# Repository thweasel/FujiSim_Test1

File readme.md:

# FujiNet Z80 simulation

The repo contains a SimulIDE simulator circuit with an Ardunio Mega to simulate Z80 and ESP signalling to the proposed bus interface.

Platform IO should be used within Visual Code to compile the project which is based on Arduino libraries.

## SimulIDE simulation settings

**SimulIDE Version0.4.15SR10**

To accurately simulate the SPI timing the properties of the simulation need to be edited before running. The "Simu Step ns" needs to be set to 10 in SimulIDE (right click empty diagram space, select properties from pop up menu). If simulation step time is not set correctly, then the ESP simulation will see bits missing when reading the Shift registers as the Clock and data signalling slips.

Don't forget to load the Firmware file into the Arduino! PlatformIO compiles the Arduino code to ./.pio/megaatmega2560/firmware.hex, when you click Build (not Build and program unless you are using real hardware!)

## KiCad ##

**KiCad version 7**

Going forward there are going to be different ways that the modules can be implemented and built. Therefore, a set of KiCad projects are in a modules folder, and then there is a folder for libraries for symbols/footprints; these are the building blocks. 

Each module project should have 2 schematics. The main project schematic has Pin headers etc. for a (test) PCB and a hierarchical schematic (not a project just a file) that contains the module's circuit. The module's hierarchical schematic file should not contain any connectors or "PCB stuff" just the parts needed for its function. So when making an adaptor the nested hierarchical schematic can be imported this hierarchical schematic without the extra "PCB stuff" cluttering the adaptor project PCBs. Module projects do not need a PCB design as they are imported into other projects that implement the PCB design and associated connectors etc. However, I like the idea of the modules being projects which have a PCB design to create a physical implementation for testing. In time all the modules could follow some common standard for PCB implementation these could be built and wired up ad-hoc.

A reference design is in the root KiCad folder, this shows how everything should connect up to make an adapter. There shouldn't really be a PCB for the reference design as the PCB design can (and did) influence the schematic. The reference design should be a pure, readable and simple expression of the requirements. So going forward a KiCad project should be created for the adaptor being built (in the adaptors folder), a simple way to copy all the settings is to save as from a similar project (e.g. template project). Now the modules schematics can be added to the adaptor project hierarchical schematics, add their hierarchical pins and wire/label as required.

If an adaptor uses a daughter board, then sub-projects in the adapter project need to be created (so they have their own PCB design). The sub-project is imported to the adaptor's main project as a hierarchical schematic so that the Electronic Rule Checker (ERC) can be used to validate the design.  Don't try to mark one-eye ball an adaptor design there are multiple busses and logic signals, and it's not far off a small computer; ERC is a valuable tool so use it. Another trick is to make use of the BUS net Class directives which apply styling to the connected bus, if a connection is missing there is no styling applied. I like to make it easy to see when things aren't connected as sometimes the ERC won't report a problem (more than one pin is connected makes it valid, even if it should be 3 pins connected).

## PCB fabrication with a 3018 CNC mill

The software pipeline:
- KiCad PCB design (export Gerber and Drill files)
- pcb2gcode (CAM, gerber to gcode)
- Universal Gcode Sender (runs the CNC mill controller)

The size and accuracy of the mill determine the PCB design rules to be used in the KiCad board setup. 

After trial and error, the following minimum limits have been found. A 0.5mm end mill (cutter) requires at a minimum, 0.4mm tracks and 0.6mm clearances. (This may change with pcb2gcode and some "git-gud"). With a 200-watt spindle motor, the following speeds and feeds for drilling and milling with a 0.5mm end mill.

Drilling
- Z cut -2mm
- Z Feedrate 30
- Spindle Speed 600 (~60% power)

Milling
- Z cut -0.15mm (board thickness varies)
- X-Y Feedrate 60 (20 or 40)
- Z Feedrate 30
- Spindle speed 800 (~80% power)

Going slower seems to be better for accuracy and success. Running the milling at max spindle speed and -1.5 cut resulted in a snapped 0.5mm end mill. Also, there is a lot of noise/vibration which makes the cutting just sound wrong.

The choice of tool for cutting the isolation paths seems to be split between V-bits and tiny straight-end mills. V-bits have a tip as narrow as 0.1mm but widen based on the angle (degrees) of the V. Assuming a perfectly flat board of even thickness, the tip + width at depth (0.1mm) isolation paths can be cut; assume a width of ~0.2mm approximately. However, perfect doesn't exist, the bit moves as Z height but the surface height changes (PCB thickness, bowing etc.). Therefore, the cut width changes as the V shape angle produces wider cuts as the tip moves deeper into the material. An end mill has a straight edge so cuts consistently at all depths below the surface. The only concern is cutting too deep and breaking the end mill, which is why a 0.5mm bit is used. End mills or Ball cutters go down to 0.2mm, but breakage risks increase. There is a similar problem with V bits, a 20-degree angle has a weaker tip than a 60-degree angle V bit. A wider angle V bit cut widens quicker with slight changes in depth. There is no perfect tool, just compromises and different workflows.

To counter problems with Vbits and depth of cut, Universal Gcode Sender has a plugin called "AutoLeveler". This plugin probes the height of the PCB at some given intervals. A height map is generated and the Z positions in the Gcode are modified. Thus, adding to the process of milling per side, probing pass and transformation of gcode. The accuracy of the trace is subject to the resolution of the probing, high accuracy means probing more points (long time). To conclude, there is room to achieve thinner track and clearance but for now, a simpler reliable approach trumps mastery of PCB milling.

Milling two-sided PCBs require the board to be flipped. This is an immediate alignment challenge which needs some thought. There are limitations imposed by CAM software features and the size of the CNC mill. Typically, the method seems to be prescribed by the CAM software. FlatCAM does inbox flips, the board is in the same place on the bed. To do this FlatCAM provides support to flip/mirror one of the Gerbers, alignment drill holes can be easily added. However, FlatCAM is too manual and buggy. 

Pcb2gcode enables "millproject" config files to be set up and reused between projects. The flip method used is a page turn by default, which requires the bed to be twice the size of the PCB. With a small bed and a big board, an in-place flip can be achieved by re-zeroing the origin on the X-axis after the flip.  Ideally, a jig should be used to maintain X-Y alignment or alternatively a pair of alignment holes evenly spaced from the centre lines. To make the flip alignment accurate an alignment hole can be drilled at 0,0 on the front; when flipped re-align to the hole and reset X 0. If you don't want to make holes in a PCB that is cut accurately to size, then zero on the corners (with the same tool fitted each time).

### KiCad PCB design/settings

Before laying out the PCB you need to set up the board settings, Design Rules and Net Classes. these should be set based on the achievable tollerances of the milling process.

Auto routing (FreeRouting) ignores the Design Rules, it only seems to follow NetClass rules, Edges and Margins (Rule areas on the margin layer). Therefore, you should fully define the board before placing components!

The process sets are:
Configure Design Rules and Net Classes
Draw an Edge box to the size of the PCB
Set Origin (file/drill/sheet) in the top left of the Edge box - place a *VIA on this spot
Create Margin boxes (+2mm) on the edges (Rule Area)
Layout components
Route tracks
Export Gerber and drill files (include the origins)
Export SVG as a CNC reference. F.Cu, B.Cu, User.Drawings, Edge.Cuts, F.Fab, B.Fab

*Directly placing a VIA on the Origin is blocked if it is in the margin. To get round this place the VIA outside the margin and move it to the Origin, this is permitted. Else you could adjust the shape of the marging and expose the corner.

Your PCB should have an Edge box the size of the PCB (stock or cut out). Marked out margins for Freerouting, 2mm seems reasonable. The Origin for sheets and files needs to be set at the top left of the Edge box. Origin can be corrected in pcb2gcode and milling just saves effort to do it right. Export to Gerber (Fabrication output), make sure "Use drill/place file origin" is checked. Hit Plot and Generate Drill Files. If you want to be tidy, export only the F.Cu, B.CU, and Edge_Cuts. You have a PCB file set to run through pcb2gcode.

The KiCad process is done!

### pcb2gcode CAM 

A "millproject" needs to be configured which enables milling a PCB with the Design Rules defined in KiCad. Yep, this is a circular dependency! 

Each Gerber needs to be addressed directly in the millproject file. Given the KiCad naming scheme, a bash script with a command line config can be used to wildcard the files. E.g. "pcb2gcode --front=*-F_Cu.gbr".

Read the wiki to create the millproject file https://github.com/pcb2gcode/pcb2gcode/wiki/Manual

Examples can be found in the pcb2gcode folder.

### Milling procedure

Set up a jig on the bed to hold the PCB.

Start with the front processes, which all have positive X co-ordinates

**Alignment**
- Align the mill and zero on the origin TOP-LEFT (same as KiCad)
- Use the PCB corner (marker pen) OR drill an alignment hole for the origin

**Drilling - front**
- Use drill bits that are the same length butted up in the collet, save  zeroing the Z axis per bit.
- Fit the first Tool (drill bit) in drill.ngc
- Touch the bit on the surface of the board and set Z to zero
- Run the drill.ngc
- Change bits as prompted.

**Milling - front**
- Fit the 0.5mm end mill
- Touch bit on the PCB surface and 0 Z axis
- Run Front.ngc

**Flip on Y (left to right)**
- The default flip/mirror axis in pcb2gcode is along the left edge of the - PCB, "turning a page in a book".
- Measure the X-axis length, move the mill from 0,0 lenght+X
- The mill should now be aligned to the TOP-RIGHT corner, opposite the origin used for the front.
- Tune positioning
- RESET X to 0

All cuts on the Back.ngc have a negative X coordinate so the mill runs from right to left.

**Milling - back**
- Fit the 0.5mm end mill
- Touch bit on the PCB surface and 0 Z axis
- Run Back.ngc

**Cut out - optional**
- Fit a cutting end mill (3.127mm)
- Touch bit on the PCB surface and 0 Z axis
- Run Outline.ngc

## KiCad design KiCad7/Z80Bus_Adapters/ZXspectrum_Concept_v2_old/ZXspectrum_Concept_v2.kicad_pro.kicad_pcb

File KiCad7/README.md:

# KiCad projects

Folders:

**Adapters** projects to make FujiNet adapters for different machines.

**Modules** parts to import into adapters for common functions e.g. SPI bus.

**Modules/*_impl** modules implemented as stand-alone PCBs with connectors

**ReferenceDesign** is an example of a completed adapter (schematic) for a ZX spectrum. This is the current concept design.

## New projects and path management

Some KiCad referencing information because managing paths is a tad annoying. Use relative pathing if you want anyone to open something you made. To do this all paths should start ${KIPRJMOD} which is the environment variable for the project folder ../ will take you back one layer as expected.

If you want to start a new Module or Adapter then you should open the template project and SAVE AS "name". This will copy the template and setting for you, and then there is less to set up.  Setting up from scratch requires libraries importing, Net classes, buses, PCB settings etc set up.

### Symbols

Name: esp32-wrover
Path: ${KIPRJMOD}/../../FujiNet_KiCadLibs/esp32-wrover-kicad-master/esp32-wrover.lib

Name: FujiNet_Memory_RAM
Path: ${KIPRJMOD}/../../FujiNet_KiCadLibs/FujiNet_Memory_RAM.kicad_sym

### Footprints
Name: esp32-wrover
Path: ${KIPRJMOD}/../../FujiNet_KiCadLibs/esp32-wrover-kicad-master/esp32-wrover.pretty

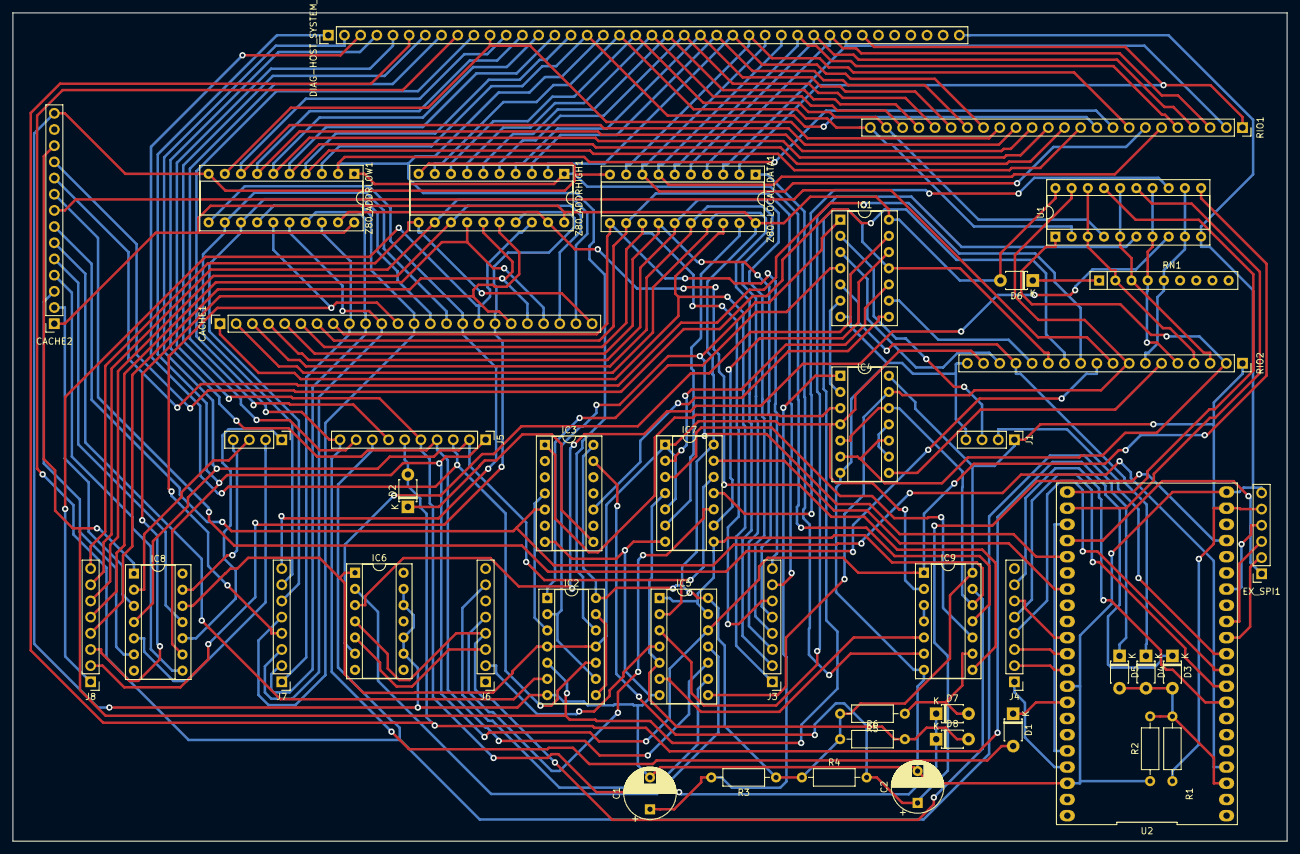
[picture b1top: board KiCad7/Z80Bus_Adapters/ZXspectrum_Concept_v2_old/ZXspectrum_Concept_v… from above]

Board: 2 copper layers, 200.0 x 130.0 mm, 45 parts (0 on the bottom side), 139 nets.

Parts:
C1, C2: 10UF; CP_Radial_D8.0mm_P5.00mm
CACHE1: Conn_01x24_Socket; PinSocket_1x24_P2.54mm_Vertical
CACHE2: Conn_01x14_Socket; PinSocket_1x14_P2.54mm_Vertical
D1, D2, D3, D4, D5, D6, D7, D8: 1N4148; D_T-1_P5.08mm_Horizontal
DIAG-HOST_SYSTEM_BUS1: DIAG-HOST_SYSTEM_BUS; PinHeader_1x40_P2.54mm_Vertical
EX_SPI1: PinSocket_2.54mm; PinSocket_1x06_P2.54mm_Vertical
IC1: 7404N; DIP-14_W7.62mm_Socket
IC2, IC5, IC7, IC9: 74HC32N; DIP-14_W7.62mm_Socket
IC3: 7474N; DIP-14_W7.62mm_Socket
IC4, IC6, IC8: 74HC08N; DIP-14_W7.62mm_Socket
J1: PinHeader_2.54mm; PinHeader_1x04_P2.54mm_Vertical
J3: LOCAL_D; PinHeader_1x08_P2.54mm_Vertical
J4: ESP_SPI_INT; PinHeader_1x08_P2.54mm_Vertical
J5: Z80_CONTROL; PinHeader_1x10_P2.54mm_Vertical
J6: ESP_CONTROL; PinHeader_1x08_P2.54mm_Vertical
J7: LOCAL_A-L; PinHeader_1x08_P2.54mm_Vertical
J8: LOCAL_A-H; PinHeader_1x08_P2.54mm_Vertical
LOCAL_CONTROL1: LOCAL_CONTROL; PinHeader_1x04_P2.54mm_Vertical
R1, R2, R3, R4: 22K; R_Axial_DIN0207_L6.3mm_D2.5mm_P10.16mm_Horizontal
R5, R6: 10K; R_Axial_DIN0207_L6.3mm_D2.5mm_P10.16mm_Horizontal
RIO1: Conn_01x24_Socket; PinSocket_1x24_P2.54mm_Vertical
RIO2: Conn_01x18_Socket; PinSocket_1x18_P2.54mm_Vertical
RN1: 4609M-101-103LF; R_Array_SIP9
U1: 74HC244N; DIP-20_W7.62mm_Socket
U2: FREENOVE_ESP32-WROVER-DEV
Z80-LOCAL_DATA1, Z80_ADDRHIGH1, Z80_ADDRLOW1: 74HC245N; DIP-20_W7.62mm_Socket

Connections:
+5V: CACHE2.1, D6.2 (A), EX_SPI1.5, IC1.14 (VCC), IC2.14 (VCC), IC3.14 (VCC), IC4.14 (VCC), IC5.14 (VCC), IC7.14 (VCC), IC9.14 (VCC), J1.1, R1.2, R3.1, R4.1, R5.2, R6.1, RIO2.1, U1.20 (VCC), U2.20 (+5V), Z80-LOCAL_DATA1.20 (VCC), Z80_ADDRHIGH1.20 (VCC), Z80_ADDRLOW1.20 (VCC)
/CACHE connector/CACHE_CONTROL.A16: CACHE2.2, IC8.3
/CACHE connector/CACHE_CONTROL.CS: CACHE2.5, IC8.11
/CACHE connector/CACHE_CONTROL.DATASTATUS+PERM_Z80_IORQ: CACHE2.6, IC2.6
/CACHE connector/CACHE_CONTROL.OE: CACHE2.4, IC8.8
/CACHE connector/CACHE_CONTROL.WE: CACHE2.3, IC8.6
/CACHE connector/CACHE_DATASTATUS: CACHE2.12, IC1.11, IC2.5, IC8.1, RIO2.13
/CACHE connector/CACHE_SEL_0: CACHE2.8, RIO2.9
/CACHE connector/CACHE_SEL_1: CACHE2.9, RIO2.10
/CACHE connector/CACHE_SEL_2: CACHE2.10, RIO2.11
/CACHE connector/CACHE_SEL_3: CACHE2.11, RIO2.12
/CACHE connector/LOCAL_A0: CACHE1.9, J7.1, Z80_ADDRLOW1.18 (B0)
/CACHE connector/LOCAL_A1: CACHE1.10, J7.2, Z80_ADDRLOW1.17 (B1)
/CACHE connector/LOCAL_A2: CACHE1.11, J7.3, Z80_ADDRLOW1.16 (B2)
/CACHE connector/LOCAL_A3: CACHE1.12, J7.4, Z80_ADDRLOW1.15 (B3)
/CACHE connector/LOCAL_A4: CACHE1.13, J7.5, Z80_ADDRLOW1.14 (B4)
/CACHE connector/LOCAL_A5: CACHE1.14, J7.6, Z80_ADDRLOW1.13 (B5)
/CACHE connector/LOCAL_A6: CACHE1.15, J7.7, Z80_ADDRLOW1.12 (B6)
/CACHE connector/LOCAL_A7: CACHE1.16, J7.8, Z80_ADDRLOW1.11 (B7)
/CACHE connector/LOCAL_A8: CACHE1.17, J8.1, Z80_ADDRHIGH1.18 (B0)
/CACHE connector/LOCAL_A9: CACHE1.18, J8.2, Z80_ADDRHIGH1.17 (B1)
/CACHE connector/LOCAL_A10: CACHE1.19, J8.3, Z80_ADDRHIGH1.16 (B2)
/CACHE connector/LOCAL_A11: CACHE1.20, J8.4, Z80_ADDRHIGH1.15 (B3)
/CACHE connector/LOCAL_A12: CACHE1.21, J8.5, Z80_ADDRHIGH1.14 (B4)
/CACHE connector/LOCAL_A13: CACHE1.22, J8.6, Z80_ADDRHIGH1.13 (B5)
/CACHE connector/LOCAL_A14: CACHE1.23, J8.7, Z80_ADDRHIGH1.12 (B6)
/CACHE connector/LOCAL_A15: CACHE1.24, J8.8, Z80_ADDRHIGH1.11 (B7)
/CACHE connector/LOCAL_D0: CACHE1.1, J3.1, Z80-LOCAL_DATA1.18 (B0)
/CACHE connector/LOCAL_D1: CACHE1.2, J3.2, Z80-LOCAL_DATA1.17 (B1)
/CACHE connector/LOCAL_D2: CACHE1.3, J3.3, Z80-LOCAL_DATA1.16 (B2)
/CACHE connector/LOCAL_D3: CACHE1.4, J3.4, Z80-LOCAL_DATA1.15 (B3)
/CACHE connector/LOCAL_D4: CACHE1.5, J3.5, Z80-LOCAL_DATA1.14 (B4)
/CACHE connector/LOCAL_D5: CACHE1.6, J3.6, Z80-LOCAL_DATA1.13 (B5)
/CACHE connector/LOCAL_D6: CACHE1.7, J3.7, Z80-LOCAL_DATA1.12 (B6)
/CACHE connector/LOCAL_D7: CACHE1.8, J3.8, Z80-LOCAL_DATA1.11 (B7)
/CACHE connector/Z80_HARDLOCK: CACHE2.7, IC3.5 (Q), U2.4 (GPIO39)
/CORE/ESP_HARDLOCK: IC1.1, IC2.2, IC2.9, U2.26 (GPIO2)
/CORE/ESP_INT: D3.2 (A), D4.2 (A), D5.2 (A), R1.1, R2.2, U2.3 (GPIO36)
/CORE/ESP_PULSE: J1.2, U2.11 (GPIO27)
/CORE/ESP_ROMSEL_0: U1.15 (2A1), U2.23 (GPIO7)
/CORE/ESP_ROMSEL_1: U1.17 (2A0), U2.22 (GPIO6)
/CORE/ESP_ROM_WR_PROTECT: IC7.13, U2.28 (GPIO4)
/CORE/ESP_SPI_INT.CE: J4.6, U2.31 (GPIO5)
/CORE/ESP_SPI_INT.MISO: J4.2, U2.33 (GPIO19)
/CORE/ESP_SPI_INT.MOSI: J4.1, U2.39 (GPIO23)
/CORE/ESP_SPI_INT.OE: J4.7, U2.8 (GPIO33)
/CORE/ESP_SPI_INT.PL: J4.5, U2.9 (GPIO25)
/CORE/ESP_SPI_INT.SCK: J4.3, U2.32 (GPIO18)
/CORE/ESP_SPI_INT.STC: J4.4, U2.10 (GPIO26)
/CORE/ESP_WAIT_RESET: C2.1, IC3.13 (~R), R4.2, U2.18 (GPIO11)
/CORE/EX_MISO: EX_SPI1.3, U2.13 (GPIO12)
/CORE/EX_MOSI: EX_SPI1.4, U2.15 (GPIO13)
/CORE/EX_SCK: EX_SPI1.2, U2.12 (GPIO14)
/CORE/EX_SS: EX_SPI1.1, U2.25 (GPIO8)
/CORE/SD_CARD_SS: U2.24 (GPIO15), U2.38 (GPIO22)
/CORE/Z80_HARDLOCK_RESET: D4.1 (K), IC1.5, RIO2.15
/GLUE/!ESP_HARDLOCK: IC1.2, J1.3
/GLUE/CLR_Z80_HARDLOCK: IC3.1 (~R), IC4.3
/GLUE/ESP_IOD_CONFIG: IC4.5, IC4.12, IC5.1, IC5.13, IC7.8, IC9.12
/GLUE/PERM_Z80_IORQ: IC2.4, IC2.11, IC4.4, IC6.1, IC7.1, IC7.5, IC8.12, IC9.2, RIO2.17
/GLUE/PRE_Z80_HARDLOCK: IC2.3, IC3.4 (~S)
/GLUE/RIO CONTROL/ROM_WR_PROTECT+Z80_WR: IC7.11, U1.13 (2A2)
/GLUE/RIO CONTROL/Z80_RD+ESP_IOD_CONFIG+PERM_Z80_IORQ: IC6.3, U1.8 (1A3)
/GLUE/RIO CONTROL/Z80_WR+ESP_IOD_CONFIG: IC5.3, U1.6 (1A2)
/GLUE/RIO_CONTROL.A14: RIO2.4, RN1.2 (R1), U1.3 (2Y0), U1.18 (1Y0)
/GLUE/RIO_CONTROL.A15: RIO2.3, RN1.3 (R2), U1.5 (2Y1), U1.16 (1Y1)
/GLUE/RIO_CONTROL.A16: IC4.6, IC4.10, RIO2.2, U1.1 (1OE)
/GLUE/RIO_CONTROL.CE: IC4.8, RIO2.6
/GLUE/RIO_CONTROL.OE: RIO2.7, RN1.5 (R4), U1.9 (2Y3), U1.12 (1Y3)
/GLUE/RIO_CONTROL.ROM_RDY: IC4.13, IC5.8, RIO2.8, U1.19 (2OE)
/GLUE/RIO_CONTROL.WE: RIO2.5, RN1.4 (R3), U1.7 (2Y2), U1.14 (1Y2)
/GLUE/WAIT_IO: IC1.9, RIO2.14
/GLUE/Z80 BUS CONTROL/!CACHE_DATASTATUS: IC1.10, IC7.2
/GLUE/Z80 BUS CONTROL/Z80_ADD_CONNECT: D7.2 (A), IC9.9, R5.1
/GLUE/Z80 BUS CONTROL/Z80_DATA_CONNECT: D8.2 (A), IC5.5, IC7.4, R6.2
/GLUE/Z80_BUS_CONTROL.Z80_ADD_DIR: IC9.11, Z80_ADDRHIGH1.1 (A->B), Z80_ADDRLOW1.1 (A->B)
/GLUE/Z80_BUS_CONTROL.Z80_ADD_OE: IC9.8, Z80_ADDRHIGH1.19 (CE), Z80_ADDRLOW1.19 (CE)
/GLUE/Z80_BUS_CONTROL.Z80_DATA_DIR: IC9.6, Z80-LOCAL_DATA1.1 (A->B)
/GLUE/Z80_BUS_CONTROL.Z80_DATA_OE: IC7.6, Z80-LOCAL_DATA1.19 (CE)
/GLUE/Z80_HARDLOCK_SET: IC1.3, RIO2.16
/RIO connector/Z80_A0: DIAG-HOST_SYSTEM_BUS1.18, IC2.12, RIO1.9, Z80_ADDRLOW1.2 (A0)
/RIO connector/Z80_A1: DIAG-HOST_SYSTEM_BUS1.17, RIO1.10, Z80_ADDRLOW1.3 (A1)
/RIO connector/Z80_A2: DIAG-HOST_SYSTEM_BUS1.16, RIO1.11, Z80_ADDRLOW1.4 (A2)
/RIO connector/Z80_A3: DIAG-HOST_SYSTEM_BUS1.15, RIO1.12, Z80_ADDRLOW1.5 (A3)
/RIO connector/Z80_A4: DIAG-HOST_SYSTEM_BUS1.14, RIO1.13, Z80_ADDRLOW1.6 (A4)
/RIO connector/Z80_A5: DIAG-HOST_SYSTEM_BUS1.13, RIO1.14, Z80_ADDRLOW1.7 (A5)
/RIO connector/Z80_A6: DIAG-HOST_SYSTEM_BUS1.12, RIO1.15, Z80_ADDRLOW1.8 (A6)
/RIO connector/Z80_A7: DIAG-HOST_SYSTEM_BUS1.11, RIO1.16, Z80_ADDRLOW1.9 (A7)
/RIO connector/Z80_A8: DIAG-HOST_SYSTEM_BUS1.26, RIO1.17, Z80_ADDRHIGH1.2 (A0)
/RIO connector/Z80_A9: DIAG-HOST_SYSTEM_BUS1.25, RIO1.18, Z80_ADDRHIGH1.3 (A1)
/RIO connector/Z80_A10: DIAG-HOST_SYSTEM_BUS1.24, RIO1.19, Z80_ADDRHIGH1.4 (A2)
/RIO connector/Z80_A11: DIAG-HOST_SYSTEM_BUS1.23, RIO1.20, Z80_ADDRHIGH1.5 (A3)
/RIO connector/Z80_A12: DIAG-HOST_SYSTEM_BUS1.22, RIO1.21, Z80_ADDRHIGH1.6 (A4)
/RIO connector/Z80_A13: DIAG-HOST_SYSTEM_BUS1.21, RIO1.22, Z80_ADDRHIGH1.7 (A5)
/RIO connector/Z80_A14: DIAG-HOST_SYSTEM_BUS1.20, RIO1.23, U1.4 (1A1), Z80_ADDRHIGH1.8 (A6)
/RIO connector/Z80_A15: DIAG-HOST_SYSTEM_BUS1.19, RIO1.24, U1.2 (1A0), Z80_ADDRHIGH1.9 (A7)
/RIO connector/Z80_D0: DIAG-HOST_SYSTEM_BUS1.34, RIO1.1, Z80-LOCAL_DATA1.2 (A0)
/RIO connector/Z80_D1: DIAG-HOST_SYSTEM_BUS1.33, RIO1.2, Z80-LOCAL_DATA1.3 (A1)
/RIO connector/Z80_D2: DIAG-HOST_SYSTEM_BUS1.32, RIO1.3, Z80-LOCAL_DATA1.4 (A2)
/RIO connector/Z80_D3: DIAG-HOST_SYSTEM_BUS1.31, RIO1.4, Z80-LOCAL_DATA1.5 (A3)
/RIO connector/Z80_D4: DIAG-HOST_SYSTEM_BUS1.30, RIO1.5, Z80-LOCAL_DATA1.6 (A4)
/RIO connector/Z80_D5: DIAG-HOST_SYSTEM_BUS1.29, RIO1.6, Z80-LOCAL_DATA1.7 (A5)
/RIO connector/Z80_D6: DIAG-HOST_SYSTEM_BUS1.28, RIO1.7, Z80-LOCAL_DATA1.8 (A6)
/RIO connector/Z80_D7: DIAG-HOST_SYSTEM_BUS1.27, RIO1.8, Z80-LOCAL_DATA1.9 (A7)
/SPI connector/ESP_CONTROL.BUSRQ: IC7.10, J6.5
/SPI connector/ESP_CONTROL.IORQ: IC6.5, J6.3
/SPI connector/ESP_CONTROL.MEMRQ: IC6.4, IC9.13, J6.4
/SPI connector/ESP_CONTROL.ROMCS: IC5.9, J6.7
/SPI connector/ESP_CONTROL.WR: IC5.4, J6.2
/SPI connector/LOCAL_CONTROL.IORQ: IC8.2, LOCAL_CONTROL1.3
/SPI connector/LOCAL_CONTROL.MEMRQ: IC8.13, LOCAL_CONTROL1.4
/SPI connector/LOCAL_CONTROL.RD: IC8.10, LOCAL_CONTROL1.1
/SPI connector/LOCAL_CONTROL.WR: IC8.5, LOCAL_CONTROL1.2
/SPI connector/Z80_CONTROL.BUSACK: D5.1 (K), DIAG-HOST_SYSTEM_BUS1.9, J5.8
/SPI connector/Z80_CONTROL.BUSRQ: D7.1 (K), D8.1 (K), DIAG-HOST_SYSTEM_BUS1.5, J5.5
/SPI connector/Z80_CONTROL.IORQ: DIAG-HOST_SYSTEM_BUS1.3, IC2.10, J5.3
/SPI connector/Z80_CONTROL.MEMRQ: DIAG-HOST_SYSTEM_BUS1.4, IC5.10, J5.4
/SPI connector/Z80_CONTROL.NMI: DIAG-HOST_SYSTEM_BUS1.7, J5.9
/SPI connector/Z80_CONTROL.RD: DIAG-HOST_SYSTEM_BUS1.1, IC5.12, IC8.9, IC9.1, J5.1, U1.11 (2A3)
/SPI connector/Z80_CONTROL.RESET: D1.2 (A), DIAG-HOST_SYSTEM_BUS1.10, J5.10
/SPI connector/Z80_CONTROL.ROMCS: DIAG-HOST_SYSTEM_BUS1.8, J5.7
/SPI connector/Z80_CONTROL.WAIT: D2.2 (A), D3.1 (K), DIAG-HOST_SYSTEM_BUS1.6, J5.6
/SPI connector/Z80_CONTROL.WR: DIAG-HOST_SYSTEM_BUS1.2, IC5.2, IC7.12, IC8.4, J5.2
GND: C1.2, C2.2, CACHE2.14, DIAG-HOST_SYSTEM_BUS1.40, EX_SPI1.6, IC1.7 (GND), IC2.7 (GND), IC3.7 (GND), IC4.7 (GND), IC5.7 (GND), IC6.9, IC6.10, IC6.12, IC6.13, IC7.7 (GND), IC9.7 (GND), J1.4, R2.1, RIO2.18, U1.10 (GND), U2.21 (GND), U2.34 (GND), U2.40 (GND), Z80-LOCAL_DATA1.10 (GND), Z80_ADDRHIGH1.10 (GND), Z80_ADDRLOW1.10 (GND)
unnamed: C1.1, IC4.1, R3.2
unnamed: D1.1 (K), U2.35 (GPIO21)
unnamed: D2.1 (K), IC3.8 (~Q)
unnamed: D6.1 (K), RN1.1 (common)
unnamed: IC1.4, IC2.1
unnamed: IC1.6, IC4.2
unnamed: IC1.12, IC7.9
unnamed: IC1.13, IC6.6
unnamed: IC2.8, IC2.13
unnamed: IC1.8, IC3.10 (~S)
unnamed: IC4.9, IC4.11
unnamed: IC5.6, IC9.5
unnamed: IC5.11, IC6.2
unnamed: IC7.3, IC9.10
unnamed: IC9.3, IC9.4

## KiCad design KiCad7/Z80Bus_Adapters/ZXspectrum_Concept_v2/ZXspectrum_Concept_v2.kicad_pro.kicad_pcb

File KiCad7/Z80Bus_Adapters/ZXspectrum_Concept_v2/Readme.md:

# ThatOldNerd's Revision 2 

ThatOldNerd's hard work to turn all the simulation circuit changes back into useable schematics and PCB layout.

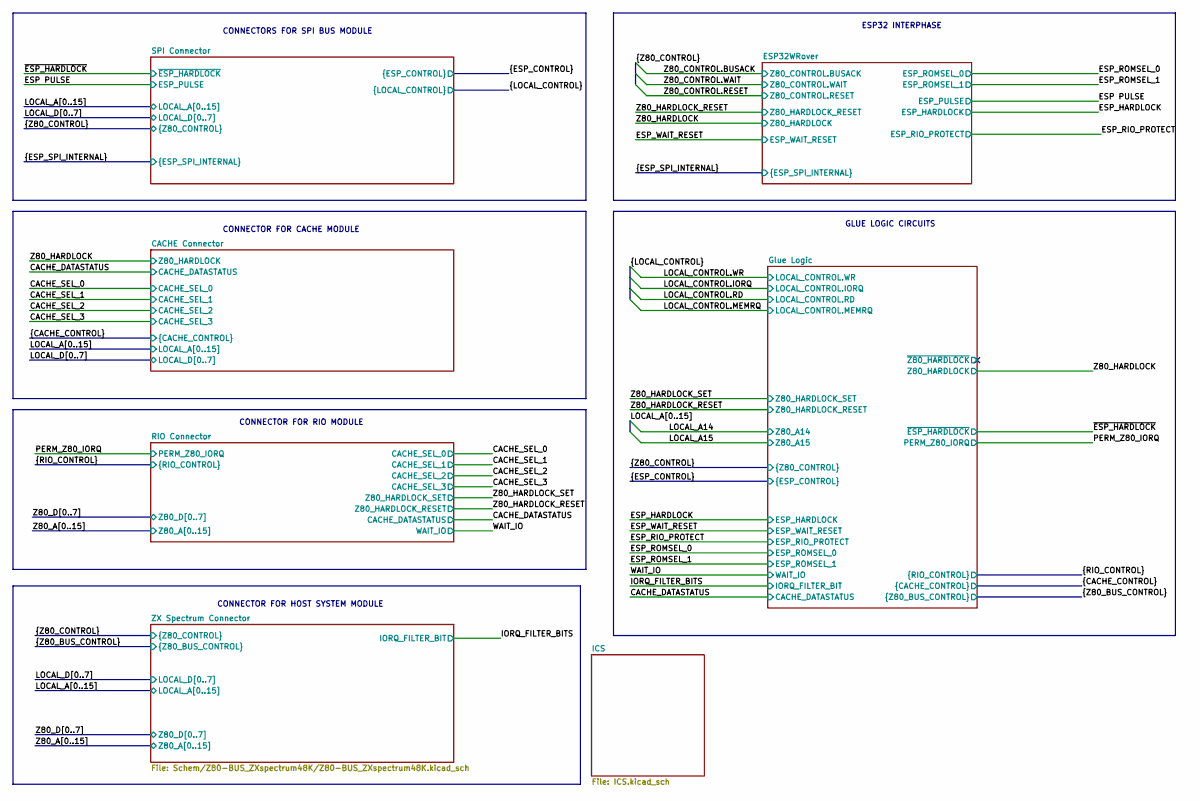
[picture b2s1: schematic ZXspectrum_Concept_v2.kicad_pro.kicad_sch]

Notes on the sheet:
CONNECTORS FOR SPI BUS MODULE
CONNECTOR FOR CACHE MODULE
CONNECTOR FOR RIO MODULE
ESP32 INTERPHASE
CONNECTOR FOR HOST SYSTEM MODULE
GLUE LOGIC CIRCUITS

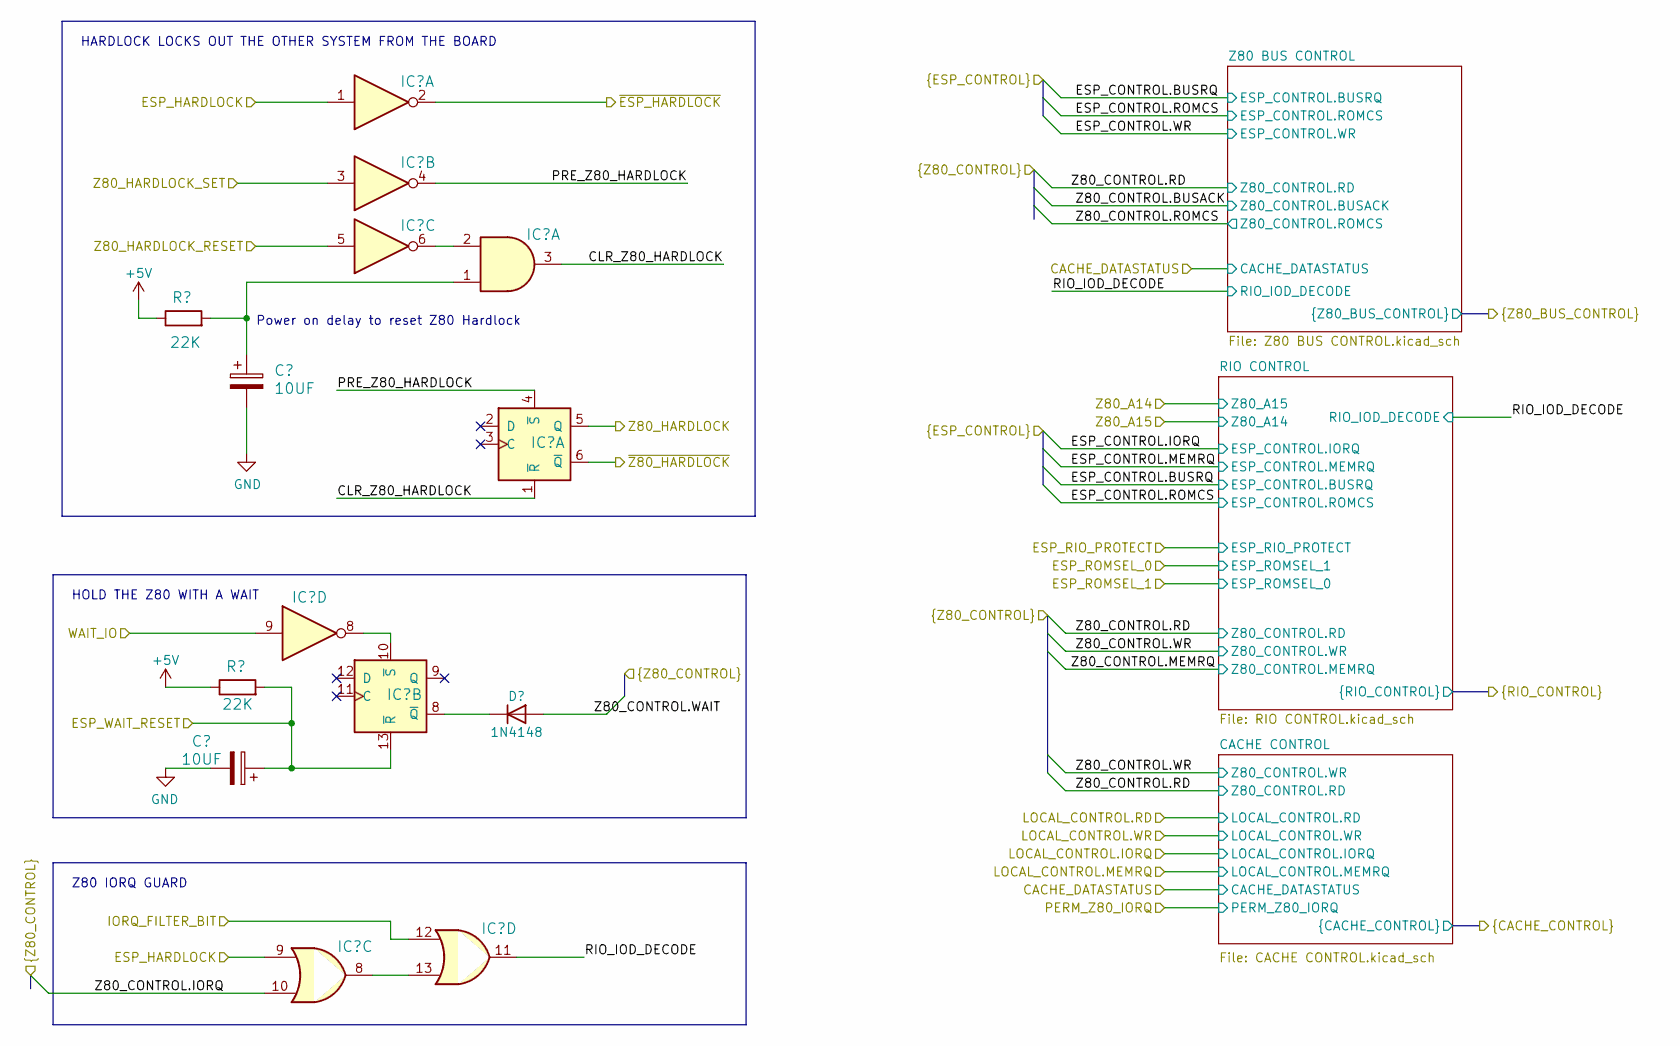
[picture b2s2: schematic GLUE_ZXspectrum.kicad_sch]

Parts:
C1, C2: 10UF; CP_Radial_D8.0mm_P5.00mm
D5: 1N4148; D_T-1_P5.08mm_Horizontal
IC1: 7404N; DIP-14_W7.62mm_Socket
IC2: 74HC32N; DIP-14_W7.62mm_Socket
IC3: 7474N; DIP-14_W7.62mm_Socket
IC4: 74HC08N; DIP-14_W7.62mm_Socket
R3, R4: 22K; R_Axial_DIN0207_L6.3mm_D2.5mm_P10.16mm_Horizontal

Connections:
+5V: IC3.14 (VCC), R3.1, R4.1; also elsewhere on the board
/ESP_CONTROL.ROMCS: IC1.13; also elsewhere on the board
/ESP_HARDLOCK: IC1.1, IC2.9; also elsewhere on the board
/ESP_WAIT_RESET: C1.1, IC3.13 (~R), R4.2; also elsewhere on the board
/Glue Logic/CLR_Z80_HARDLOCK: IC3.1 (~R), IC4.3
/Glue Logic/PRE_Z80_HARDLOCK: IC1.4, IC3.4 (~S)
/Glue Logic/~Z80_HARDLOCK: IC3.6 (~Q)
/IORQ_FILTER_BITS: IC2.12; also elsewhere on the board
/WAIT_IO: IC1.9; also elsewhere on the board
/Z80_CONTROL.IORQ: IC2.10; also elsewhere on the board
/Z80_CONTROL.ROMCS: IC1.12; also elsewhere on the board
/Z80_CONTROL.WAIT: D5.2 (A); also elsewhere on the board
/Z80_HARDLOCK: IC3.5 (Q); also elsewhere on the board
/Z80_HARDLOCK_RESET: IC1.5; also elsewhere on the board
/Z80_HARDLOCK_SET: IC1.3; also elsewhere on the board
unnamed: IC2.8, IC2.13
unnamed: IC1.8, IC3.10 (~S)

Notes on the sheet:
HARDLOCK LOCKS OUT THE OTHER SYSTEM FROM THE BOARD
Power on delay to reset Z80 Hardlock
HOLD THE Z80 WITH A WAIT
Z80 IORQ GUARD

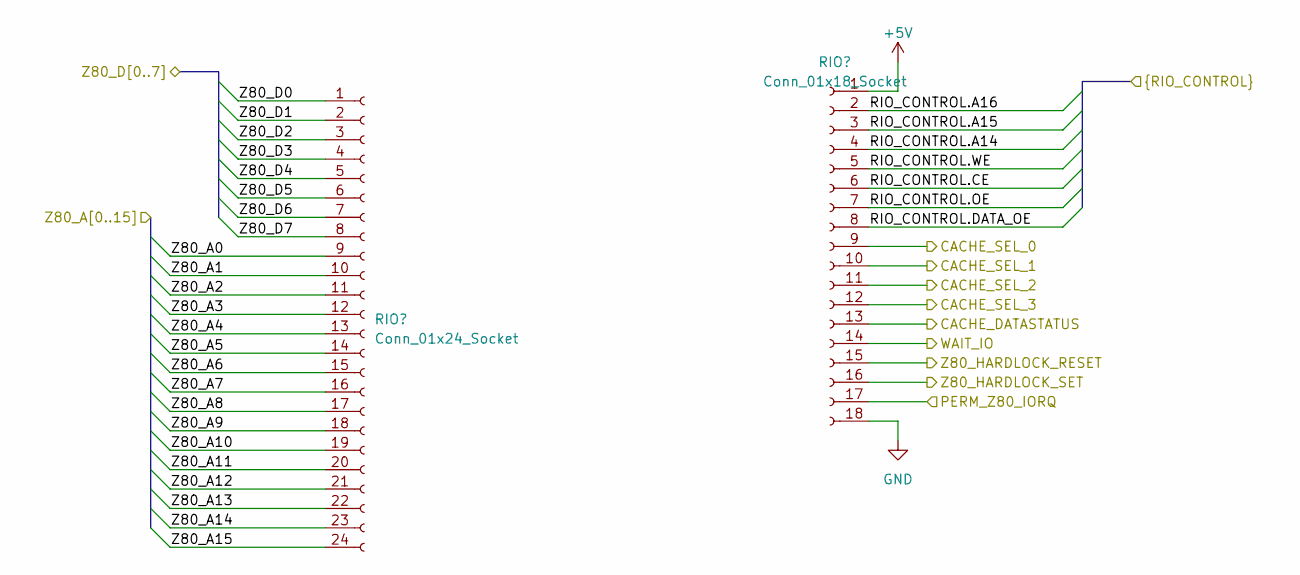
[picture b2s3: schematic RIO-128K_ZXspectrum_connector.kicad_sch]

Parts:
RIO1: Conn_01x24_Socket; PinSocket_1x24_P2.54mm_Vertical
RIO2: Conn_01x18_Socket; PinSocket_1x18_P2.54mm_Vertical

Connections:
+5V: RIO2.1; also elsewhere on the board
/CACHE_SEL_0: RIO2.9; also elsewhere on the board
/CACHE_SEL_1: RIO2.10; also elsewhere on the board
/CACHE_SEL_2: RIO2.11; also elsewhere on the board
/CACHE_SEL_3: RIO2.12; also elsewhere on the board
/PERM_Z80_IORQ: RIO2.17; also elsewhere on the board
/RIO_CONTROL.A14: RIO2.4; also elsewhere on the board
/RIO_CONTROL.A15: RIO2.3; also elsewhere on the board
/RIO_CONTROL.CE: RIO2.6; also elsewhere on the board
/RIO_CONTROL.OE: RIO2.7; also elsewhere on the board
/RIO_CONTROL.WE: RIO2.5; also elsewhere on the board
/WAIT_IO: RIO2.14; also elsewhere on the board
/Z80_A0: RIO1.9; also elsewhere on the board
/Z80_A1: RIO1.10; also elsewhere on the board
/Z80_A2: RIO1.11; also elsewhere on the board
/Z80_A3: RIO1.12; also elsewhere on the board
/Z80_A4: RIO1.13; also elsewhere on the board
/Z80_A5: RIO1.14; also elsewhere on the board
/Z80_A6: RIO1.15; also elsewhere on the board
/Z80_A7: RIO1.16; also elsewhere on the board
/Z80_A8: RIO1.17; also elsewhere on the board
/Z80_A9: RIO1.18; also elsewhere on the board
/Z80_A10: RIO1.19; also elsewhere on the board
/Z80_A11: RIO1.20; also elsewhere on the board
/Z80_A12: RIO1.21; also elsewhere on the board
/Z80_A13: RIO1.22; also elsewhere on the board
/Z80_A14: RIO1.23; also elsewhere on the board
/Z80_A15: RIO1.24; also elsewhere on the board
/Z80_D0: RIO1.1; also elsewhere on the board
/Z80_D1: RIO1.2; also elsewhere on the board
/Z80_D2: RIO1.3; also elsewhere on the board
/Z80_D3: RIO1.4; also elsewhere on the board
/Z80_D4: RIO1.5; also elsewhere on the board
/Z80_D5: RIO1.6; also elsewhere on the board
/Z80_D6: RIO1.7; also elsewhere on the board
/Z80_D7: RIO1.8; also elsewhere on the board
/Z80_HARDLOCK_RESET: RIO2.15; also elsewhere on the board
/Z80_HARDLOCK_SET: RIO2.16; also elsewhere on the board

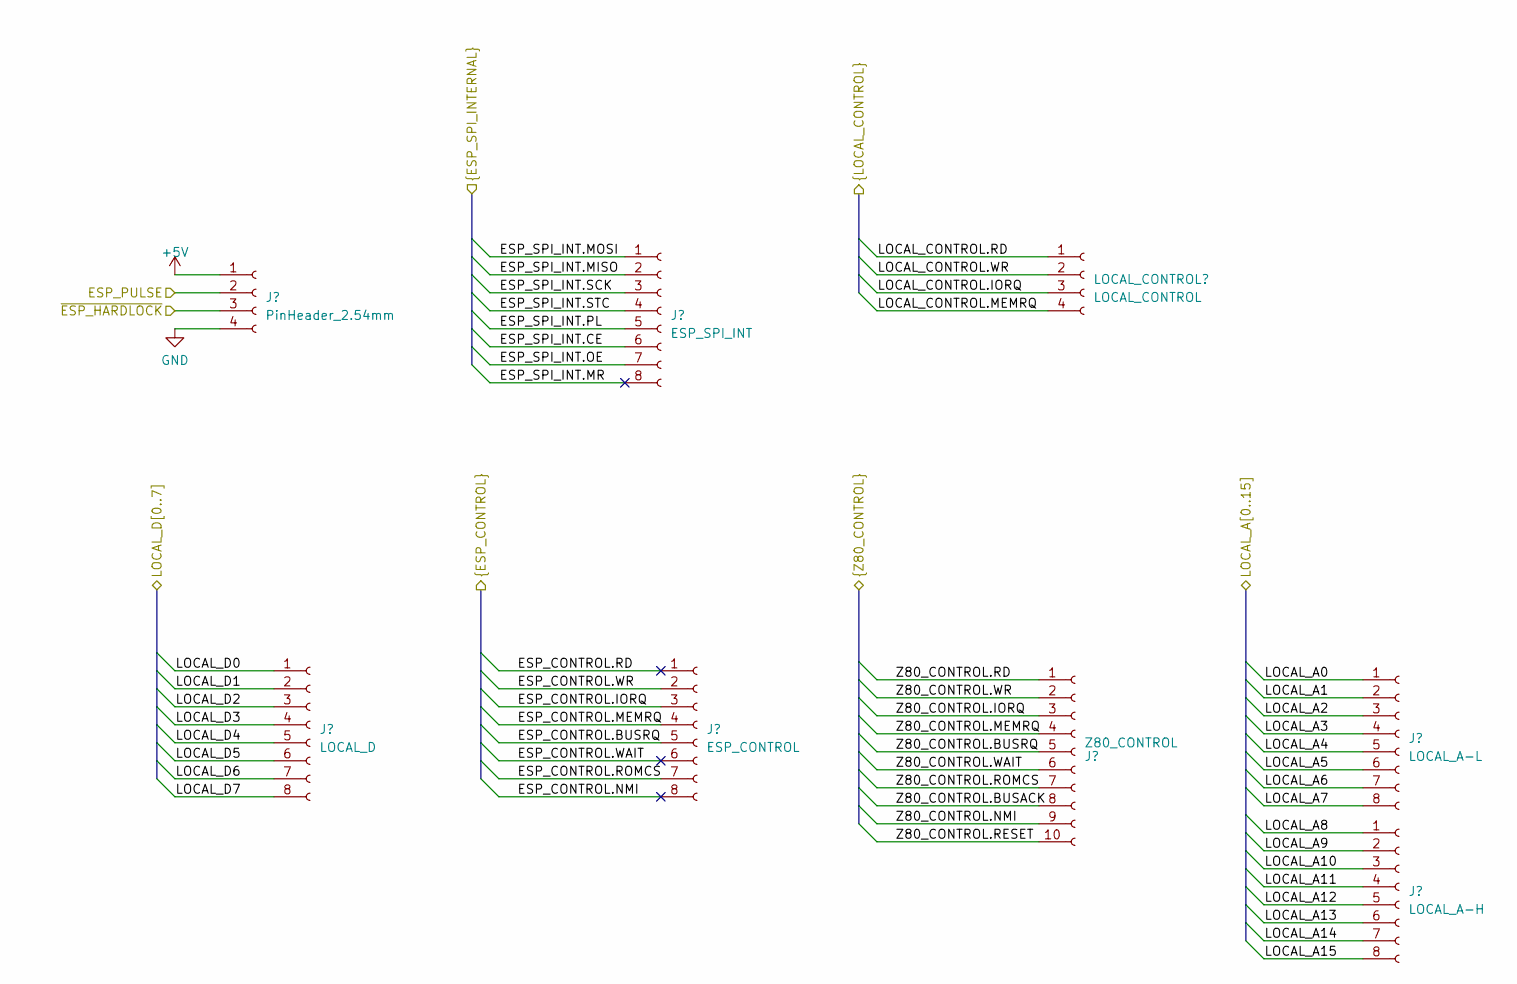
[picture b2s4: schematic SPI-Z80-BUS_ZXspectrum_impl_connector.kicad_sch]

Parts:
J1: PinHeader_2.54mm; PinHeader_1x04_P2.54mm_Vertical
J2: LOCAL_D; PinHeader_1x08_P2.54mm_Vertical
J3: ESP_SPI_INT; PinHeader_1x08_P2.54mm_Vertical
J4: ESP_CONTROL; PinHeader_1x08_P2.54mm_Vertical
J5: Z80_CONTROL; PinHeader_1x10_P2.54mm_Vertical
J6: LOCAL_A-L; PinHeader_1x08_P2.54mm_Vertical
J7: LOCAL_A-H; PinHeader_1x08_P2.54mm_Vertical
LOCAL_CONTROL1: LOCAL_CONTROL; PinHeader_1x04_P2.54mm_Vertical

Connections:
+5V: J1.1; also elsewhere on the board
/ESP PULSE: J1.2; also elsewhere on the board
/ESP_CONTROL.BUSRQ: J4.5; also elsewhere on the board
/ESP_CONTROL.IORQ: J4.3; also elsewhere on the board
/ESP_CONTROL.MEMRQ: J4.4; also elsewhere on the board
/ESP_CONTROL.NMI: J4.8
/ESP_CONTROL.RD: J4.1
/ESP_CONTROL.ROMCS: J4.7; also elsewhere on the board
/ESP_CONTROL.WAIT: J4.6
/ESP_CONTROL.WR: J4.2; also elsewhere on the board
/ESP_SPI_INT.CE: J3.6; also elsewhere on the board
/ESP_SPI_INT.MISO: J3.2; also elsewhere on the board
/ESP_SPI_INT.MOSI: J3.1; also elsewhere on the board
/ESP_SPI_INT.MR: J3.8
/ESP_SPI_INT.OE: J3.7; also elsewhere on the board
/ESP_SPI_INT.PL: J3.5; also elsewhere on the board
/ESP_SPI_INT.SCK: J3.3; also elsewhere on the board
/ESP_SPI_INT.STC: J3.4; also elsewhere on the board
/LOCAL_A0: J6.1; also elsewhere on the board
/LOCAL_A1: J6.2; also elsewhere on the board
/LOCAL_A2: J6.3; also elsewhere on the board
/LOCAL_A3: J6.4; also elsewhere on the board
/LOCAL_A4: J6.5; also elsewhere on the board
/LOCAL_A5: J6.6; also elsewhere on the board
/LOCAL_A6: J6.7; also elsewhere on the board
/LOCAL_A7: J6.8; also elsewhere on the board
/LOCAL_A8: J7.1; also elsewhere on the board
/LOCAL_A9: J7.2; also elsewhere on the board
/LOCAL_A10: J7.3; also elsewhere on the board
/LOCAL_A11: J7.4; also elsewhere on the board
/LOCAL_A12: J7.5; also elsewhere on the board
/LOCAL_A13: J7.6; also elsewhere on the board
/LOCAL_CONTROL.IORQ: LOCAL_CONTROL1.3; also elsewhere on the board
/LOCAL_CONTROL.MEMRQ: LOCAL_CONTROL1.4; also elsewhere on the board
/LOCAL_CONTROL.RD: LOCAL_CONTROL1.1; also elsewhere on the board
/LOCAL_CONTROL.WR: LOCAL_CONTROL1.2; also elsewhere on the board
/LOCAL_D0: J2.1; also elsewhere on the board
/LOCAL_D1: J2.2; also elsewhere on the board
/LOCAL_D2: J2.3; also elsewhere on the board
/LOCAL_D3: J2.4; also elsewhere on the board
/LOCAL_D4: J2.5; also elsewhere on the board
/LOCAL_D5: J2.6; also elsewhere on the board
/LOCAL_D6: J2.7; also elsewhere on the board
/LOCAL_D7: J2.8; also elsewhere on the board
/Z80_CONTROL.BUSACK: J5.8; also elsewhere on the board
/Z80_CONTROL.BUSRQ: J5.5; also elsewhere on the board
/Z80_CONTROL.IORQ: J5.3; also elsewhere on the board
/Z80_CONTROL.NMI: J5.9; also elsewhere on the board
/Z80_CONTROL.RESET: J5.10; also elsewhere on the board
/Z80_CONTROL.ROMCS: J5.7; also elsewhere on the board
/Z80_CONTROL.WAIT: J5.6; also elsewhere on the board
/Z80_CONTROL.WR: J5.2; also elsewhere on the board
